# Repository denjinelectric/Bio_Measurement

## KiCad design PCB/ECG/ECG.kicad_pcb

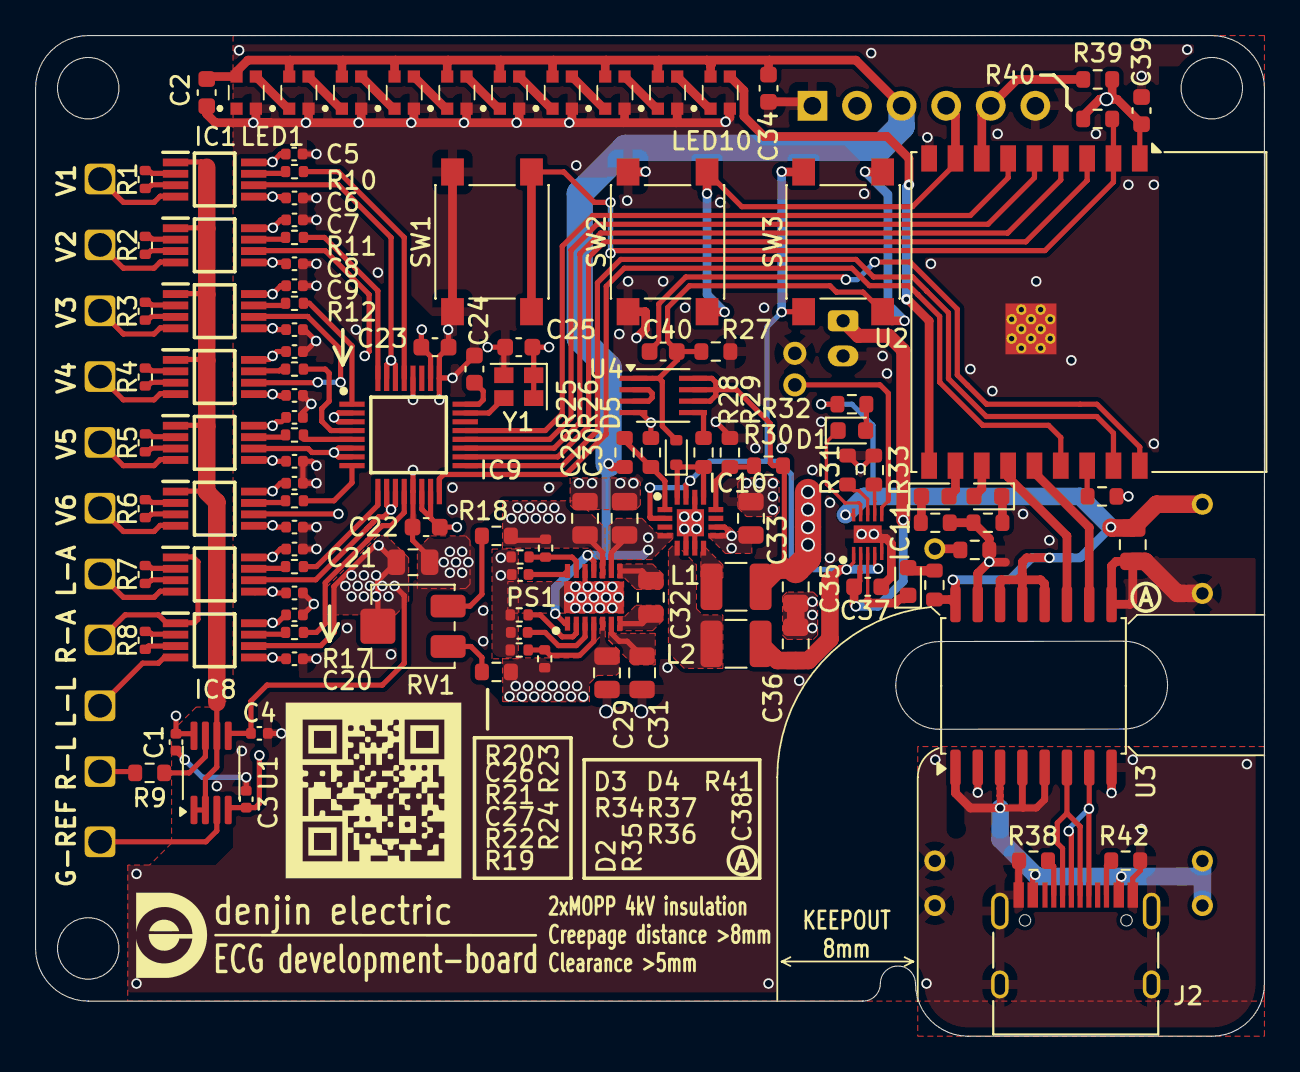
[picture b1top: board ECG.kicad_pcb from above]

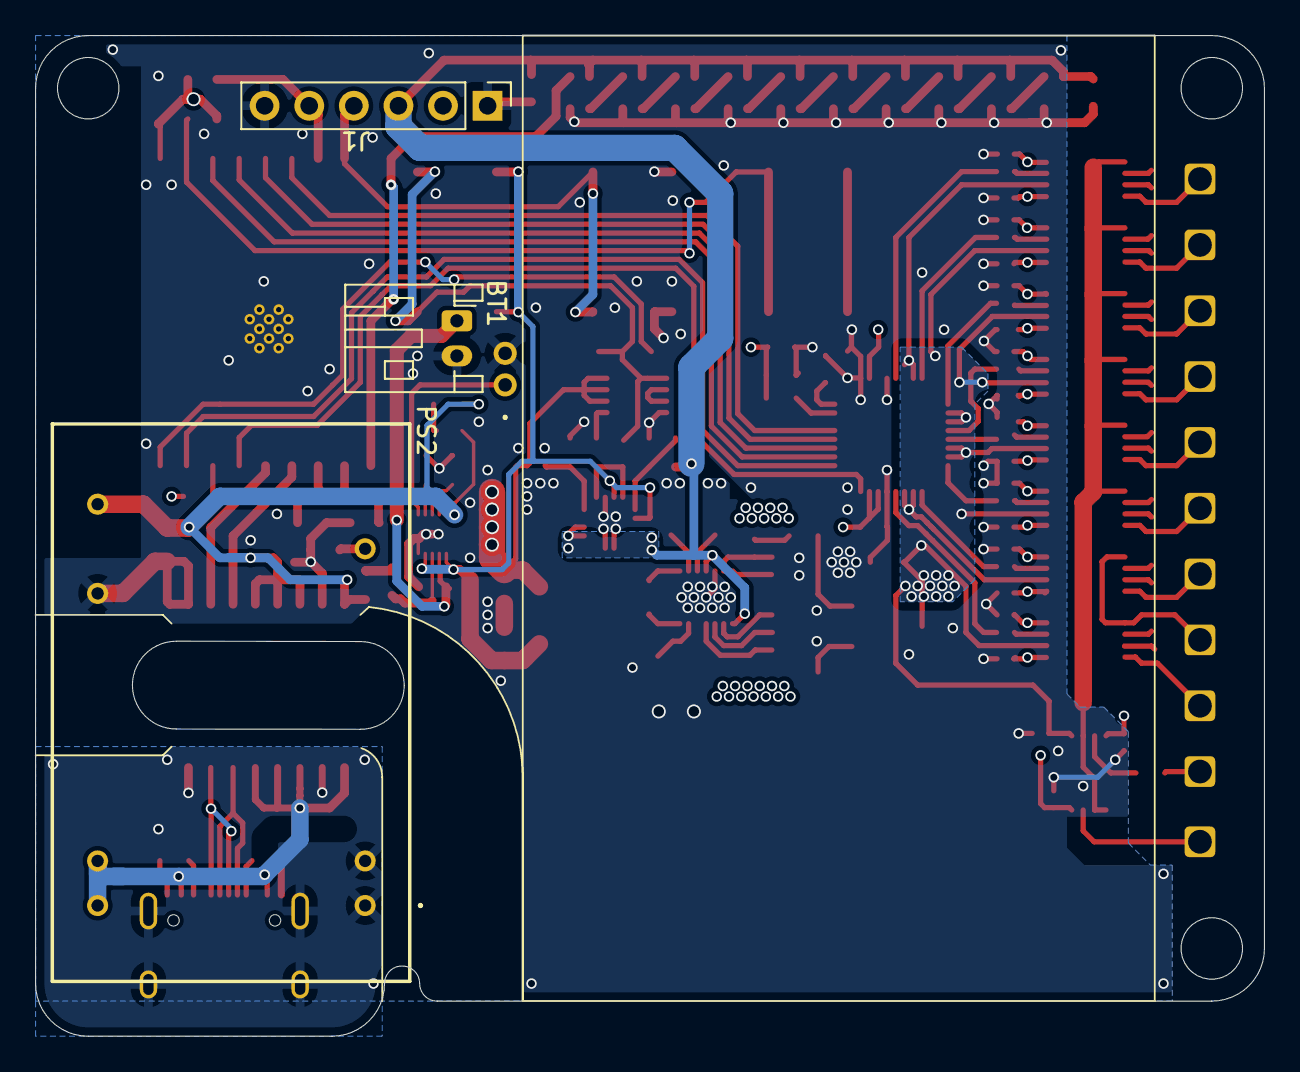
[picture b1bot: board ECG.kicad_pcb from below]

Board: 4 copper layers, 70.0 x 57.0 mm, 137 parts (4 on the bottom side), 115 nets.

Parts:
 : LOGO; logo2
BT1: Battery_Cell; JST_PH_S2B-PH-K_1x02_P2.00mm_Horizontal
C1, C3, C4, C5, C6, C7, C8, C9, C10, C11, C12, C13, C14, C15, C16, C17, C18, C19, C20, C26, C27: 0.01uF; C_0402_1005Metric
C2, C25, C34, C37, C39: 0.1u; C_0603_1608Metric
C21, C30, C32, C33, C35, C36, C38: 1u; C_0805_2012Metric
C22, C23: 1u; C_0603_1608Metric
C24: 0.22u; C_0603_1608Metric
C28, C29, C31: 10uF; C_0805_2012Metric
C40: 0.01uF; C_0603_1608Metric
D1, D2, D3, D4: LED; LED_0603_1608Metric
D5: RB520S; D_SOD-523
IC1, IC2, IC3, IC4, IC5, IC6, IC7, IC8: AD8220BRMZ-RL; SOP65P490X110-8N
IC9: ADS131M08IPBS; QFP50P700X700X120-32N
IC10: LTC3523EUD-2#TRPBF; QFN50P300X300X80-17N-D
IC11: BQ25185DLHR; SON40P220X200X80-11N
J1: Conn_01x06_Socket; PinHeader_1x06_P2.54mm_Vertical
J2: USB_C_Receptacle_USB2.0_16P; USB_C_Receptacle_HRO_TYPE-C-31-M-12
L1, L2: 4.7uH; L_1210_3225Metric
LED1, LED2, LED3, LED4, LED5, LED6, LED7, LED8, LED9, LED10: WS2812C-2020; WS2812C2020
PS1: LTC3260IDE#PBF; SON50P300X400X80-15N-D
PS2: JHM1005S05
R1, R2, R3, R4, R5, R6, R7, R8: 499±0.1%; R_0402_1005Metric
R9, R32, R36: 1k; R_0603_1608Metric
R10, R11, R12, R13, R14, R15, R16, R17: 10k±0.1%; R_0402_1005Metric
R18, R19, R28, R34, R37, R39, R40, R41: 10k; R_0603_1608Metric
R20, R22: 12k±0.25%; R_0402_1005Metric
R21: 100k; R_0402_1005Metric
R23: 21k±0.25%; R_0402_1005Metric
R24: 1k±0.25%; R_0402_1005Metric
R25: 15K±0.5%; R_0603_1608Metric
R26: 4.7k±0.5%; R_0603_1608Metric
R27: 40k; R_0603_1608Metric
R29: 4K±0.5%; R_0603_1608Metric
R30: 18k±0.5%; R_0603_1608Metric
R31, R33, R35, R38, R42: 5k±0.1%; R_0603_1608Metric
RV1: 10k; Potentiometer_Bourns_3314J_Vertical
SW1, SW2, SW3: SW_Push; SW_SPST_PTS645
TH1: 10k NTC; 103JT050
TP1, TP2, TP3, TP4, TP5, TP6, TP7, TP8, TP9, TP10, TP11: Pin socket; RI-1S0-SG4.2SMT
U1: AD8606ARM; MSOP-8_3x3mm_P0.65mm
U2: ESP32-C3-WROOM-02
U3: ADUM4160; SOIC-16W_7.5x10.3mm_P1.27mm
U4: TC74WH74FU; SSOP-8_2.95x2.8mm_P0.65mm
Y1: SG-210STF; Oscillator_SMD_SeikoEpson_SG210-4Pin_2.5x2.0mm

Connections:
+5V: C2.1, C30.1, C33.1, C34.1, IC10.4 (VOUT), IC10.9 (VIN2), IC10.10 (MODE), J1.3, LED1.4 (VDD), LED2.4 (VDD), LED3.4 (VDD), LED4.4 (VDD), LED5.4 (VDD), LED6.4 (VDD), LED7.4 (VDD), LED8.4 (VDD), LED9.4 (VDD), LED10.4 (VDD), PS1.1 (EN+), PS1.9 (VIN), PS1.11 (EN-), R25.2
+BATT: C36.1, IC10.2 (VIN1), IC10.15 (VBAT), IC11.1 (SYS), IC11.4 (~CE), L2.1, SW3.2
-5V: C31.2, PS1.6 (VOUT)
CLK: IC9.23 (XTAL1/CLKIN), Y1.3 (OUT)
CS0: IC9.17 (~CS), U2.17 (IO1)
DIN: IC9.21 (DIN), U2.6 (IO7)
DOUT: IC9.20 (DOUT), U2.5 (IO6)
DRDY: IC9.18 (~DRDY), U2.3 (IO4)
GND: C4.1, C21.1, IC1.6 (REF), IC2.6 (REF), IC3.6 (REF), IC4.6 (REF), IC5.6 (REF), IC6.6 (REF), IC7.6 (REF), IC8.6 (REF), IC9.2 (AIN2N), IC9.3 (AIN3N), IC9.6 (AIN4N), IC9.7 (AIN5N), IC9.10 (AIN6N), IC9.11 (AIN7N), IC9.30 (AIN0N), IC9.31 (AIN1N), RV1.2, U1.5 (+)
GND2: J2.A1 (GND), J2.A12 (GND), J2.B1 (GND), J2.B12 (GND), J2.S1 (SHIELD), PS2.2 (-VIN_1), PS2.3 (-VIN_2), R38.1, R42.1, U3.2 (GND1), U3.8 (GND1)
GNDPWR: BT1.2 (-), C1.2, C2.2, C3.2, C4.2, C5.2, C6.2, C7.2, C8.2, C9.2, C10.2, C11.2, C12.2, C13.2, C14.2, C15.2, C16.2, C17.2, C18.2, C19.2, C20.2, C21.2, C22.1, C23.1, C24.1, C25.2, C26.2, C27.2, C28.1, C29.1, C30.2, C31.1, C33.2, C34.2, C35.2, C36.2, C37.2, C38.2, C39.2, IC9.13 (AGND_1), IC9.25 (DGND), IC9.28 (AGND_2), IC10.6 (GND1), IC10.7 (GND2), IC10.14 (GND3), IC10.17 (GND), IC11.5 (GND), IC11.11 (EP), J1.1, J1.6, LED1.2 (GND), LED2.2 (GND), LED3.2 (GND), LED4.2 (GND), LED5.2 (GND), LED6.2 (GND), LED7.2 (GND), LED8.2 (GND), LED9.2 (GND), LED10.2 (GND), PS1.12 (MODE), PS1.15 (GND), PS2.16 (-VOUT), R20.2, R21.2, R22.2, R26.1, R27.1, R29.2, R31.1, R33.1, R34.2, R36.1, R37.2, SW1.1, SW2.1, TH1.2, U2.9 (GND), U2.19 (GND), U3.9 (GND2), U3.15 (GND2), U4.4 (GND), Y1.2 (GND)
GNDREF: IC1.1 (-IN), IC2.1 (-IN), IC3.1 (-IN), IC4.1 (-IN), IC5.1 (-IN), IC6.1 (-IN), U1.1, U1.2 (-), U1.6 (-)
GNDREF-in: TP11.1, U1.3 (+)
I: IC9.9 (AIN6P), R16.1
II: IC9.12 (AIN7P), R17.1
L-ARM: IC7.4 (+IN), TP7.1
L-LEG: IC8.4 (+IN), TP9.1
unnamed: BT1.1 (+), C37.1, IC11.2 (BAT)
unnamed: D1.2 (A), R32.1
unnamed: D1.1 (K), IC11.9 (STAT1)
unnamed: D2.2 (A), R35.1
unnamed: D2.1 (K), IC11.3 (STAT2)
unnamed: D3.2 (A), U2.11 (IO20/RXD)
unnamed: D3.1 (K), R34.1
unnamed: D4.2 (A), U2.12 (IO21/TXD)
unnamed: D4.1 (K), R37.1
unnamed: C40.1, D5.2 (A), R27.2, SW3.1, U4.1 (C)
unnamed: D5.1 (K), IC10.13 (~SHDN2), IC10.16 (~SHDN1), R28.2
unnamed: IC1.4 (+IN), TP1.1
unnamed: IC1.2 (RG_1), R1.2
unnamed: IC1.3 (RG_2), R1.1
unnamed: IC1.7 (VOUT), R10.2
unnamed: IC2.4 (+IN), TP2.1
unnamed: IC2.2 (RG_1), R2.2
unnamed: IC2.3 (RG_2), R2.1
unnamed: IC2.7 (VOUT), R11.2
unnamed: IC3.4 (+IN), TP3.1
unnamed: IC3.2 (RG_1), R3.2
unnamed: IC3.3 (RG_2), R3.1
unnamed: IC3.7 (VOUT), R12.2
unnamed: IC4.4 (+IN), TP4.1
unnamed: IC4.2 (RG_1), R4.2
unnamed: IC4.3 (RG_2), R4.1
unnamed: IC4.7 (VOUT), R13.2
unnamed: IC5.4 (+IN), TP5.1
unnamed: IC5.2 (RG_1), R5.2
unnamed: IC5.3 (RG_2), R5.1
unnamed: IC5.7 (VOUT), R14.2
unnamed: IC6.4 (+IN), TP6.1
unnamed: IC6.2 (RG_1), R6.2
unnamed: IC6.3 (RG_2), R6.1
unnamed: IC6.7 (VOUT), R15.2
unnamed: IC7.2 (RG_1), R7.2
unnamed: IC7.3 (RG_2), R7.1
unnamed: IC7.7 (VOUT), R16.2
unnamed: IC8.2 (RG_1), R8.2
unnamed: IC8.3 (RG_2), R8.1
unnamed: IC8.7 (VOUT), R17.2
unnamed: C24.2, IC9.24 (CAP)
unnamed: IC10.1 (FB1), R25.1, R26.2
unnamed: IC10.12 (FB2), R29.1, R30.2
unnamed: IC10.5 (SW1), L2.2
unnamed: IC10.8 (SW2), L1.1
unnamed: IC11.7 (ILIM/VSET), R33.2
unnamed: C38.1, IC11.10 (IN), PS2.14 (+VOUT), R32.2, R35.2, U3.12 (PIN), U3.13 (SPD), U3.14 (VDD2), U3.16 (VBUS2)
unnamed: IC11.8 (ISET), R31.2
unnamed: IC11.6 (TS/MR), TH1.1
unnamed: J2.A5 (CC1), R38.2
unnamed: J2.B5 (CC2), R42.2
unnamed: LED1.3 (DI), LED2.1 (DO)
unnamed: LED2.3 (DI), LED3.1 (DO)
unnamed: LED3.3 (DI), LED4.1 (DO)
unnamed: LED4.3 (DI), LED5.1 (DO)
unnamed: LED5.3 (DI), LED6.1 (DO)
unnamed: LED6.3 (DI), LED7.1 (DO)
unnamed: LED7.3 (DI), LED8.1 (DO)
unnamed: LED8.3 (DI), LED9.1 (DO)
unnamed: LED10.3 (DI), U2.10 (IO10)
unnamed: LED9.3 (DI), LED10.1 (DO)
unnamed: PS1.13 (ADJ+), R20.1, R23.1
unnamed: PS1.4 (ADJ-), R22.1, R24.1
unnamed: C26.1, PS1.14 (BYP+)
unnamed: C27.1, PS1.3 (BYP-)
unnamed: C32.1, PS1.8 (C+)
unnamed: C32.2, PS1.7 (C-)
unnamed: PS1.2 (RT), R21.1
unnamed: J2.A4 (VBUS), J2.A9 (VBUS), J2.B4 (VBUS), J2.B9 (VBUS), PS2.22 (+VIN_1), PS2.23 (+VIN_2), U3.1 (VBUS1), U3.3 (VDD1), U3.4 (PDEN), U3.5 (SPU)
unnamed: PS2.10 (TRIM), R36.2
unnamed: R9.1, U1.7
unnamed: R18.1, RV1.1
unnamed: R19.2, RV1.3
unnamed: R40.1, SW1.2, U2.2 (EN)
unnamed: R41.1, U2.16 (IO2)
unnamed: J2.A6 (D+), J2.B6 (D+), U3.7 (UD+)
unnamed: J2.A7 (D-), J2.B7 (D-), U3.6 (UD-)
unnamed: U4.2 (D), U4.3 (~Q)
unnamed: R28.1, U4.5 (Q)
PWR-OFF: C40.2, U2.18 (IO0)
R-ARM: IC7.1 (-IN), IC8.1 (-IN), TP8.1
R-LEG: R9.2, TP10.1
SCL: J1.4, SW2.2, U2.8 (IO9)
SCLK: IC9.19 (SCLK), U2.4 (IO5)
SDA: J1.5, R39.1, U2.7 (IO8)
SYNC/RESET: IC9.16 (~SYNC/~RESET), U2.15 (IO3)
USB_D+: U2.14 (IO19), U3.10 (DD+)
USB_D-: U2.13 (IO18), U3.11 (DD-)
V1: IC9.29 (AIN0P), R10.1
V2: IC9.32 (AIN1P), R11.1
V3: IC9.1 (AIN2P), R12.1
V4: IC9.4 (AIN3P), R13.1
V5: IC9.5 (AIN4P), R14.1
V6: IC9.8 (AIN5P), R15.1
VCC: C1.1, C5.1, C7.1, C9.1, C11.1, C13.1, C15.1, C17.1, C19.1, C22.2, C28.2, IC1.8 (+VS), IC2.8 (+VS), IC3.8 (+VS), IC4.8 (+VS), IC5.8 (+VS), IC6.8 (+VS), IC7.8 (+VS), IC8.8 (+VS), IC9.14 (REFIN), IC9.15 (AVDD), PS1.10 (LDO+), R18.2, R23.2, U1.8 (V+)
VDD: C23.2, C25.1, C35.1, C39.1, IC9.26 (DVDD), J1.2, L1.2, R30.1, R39.2, R40.2, R41.2, U2.1 (3V3), U4.6 (~CLR), U4.7 (~PRE), U4.8 (VCC), Y1.1 (~ST), Y1.4 (Vcc)
VSS: C3.1, C6.1, C8.1, C10.1, C12.1, C14.1, C16.1, C18.1, C20.1, C29.2, IC1.5 (-VS), IC2.5 (-VS), IC3.5 (-VS), IC4.5 (-VS), IC5.5 (-VS), IC6.5 (-VS), IC7.5 (-VS), IC8.5 (-VS), PS1.5 (LDO-), R19.1, R24.2, U1.4 (V-)

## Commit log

2026-01-29 poops
2026-01-29 ignore
2026-01-29 PCBadd
2026-01-29 PCBdelete
